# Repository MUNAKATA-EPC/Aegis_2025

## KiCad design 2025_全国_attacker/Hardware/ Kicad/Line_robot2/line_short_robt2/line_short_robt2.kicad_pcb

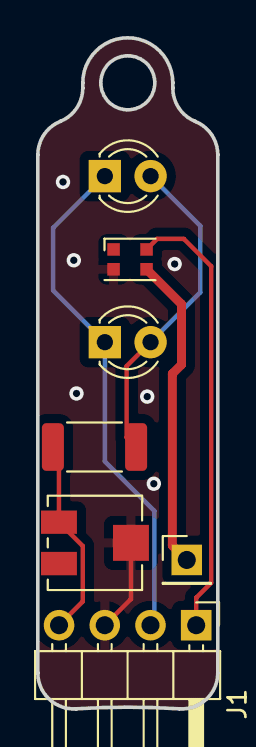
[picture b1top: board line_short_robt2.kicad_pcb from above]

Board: 2 copper layers, 10.0 x 37.3 mm, 7 parts (0 on the bottom side), 6 nets.

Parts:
D1: NeoPixel_THT; LED_WS2812B-2020_PLCC4_2.0x2.0mm
J1: Conn_01x04_Pin; PinHeader_1x04_P2.54mm_Horizontal
J2: Conn_01x01_Pin; PinHeader_1x01_P2.54mm_Vertical
Q1, Q2: Q_Photo_NPN; LED_D3.0mm_Clear
R1: 1K; R_2010_5025Metric
RV1: R_Potentiometer_Trim_US; Potentiometer_Vishay_TS53YJ_Vertical

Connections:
+3.3V: J1.2, Q1.1 (C), Q2.1 (C)
+5V: D1.3 (VDD), J2.1
/PWM: D1.4 (DIN), J1.1
/S: J1.4, R1.1, RV1.3
GND: D1.2 (GND), J1.3, RV1.2
unnamed: Q1.2 (E), Q2.2 (E), R1.2

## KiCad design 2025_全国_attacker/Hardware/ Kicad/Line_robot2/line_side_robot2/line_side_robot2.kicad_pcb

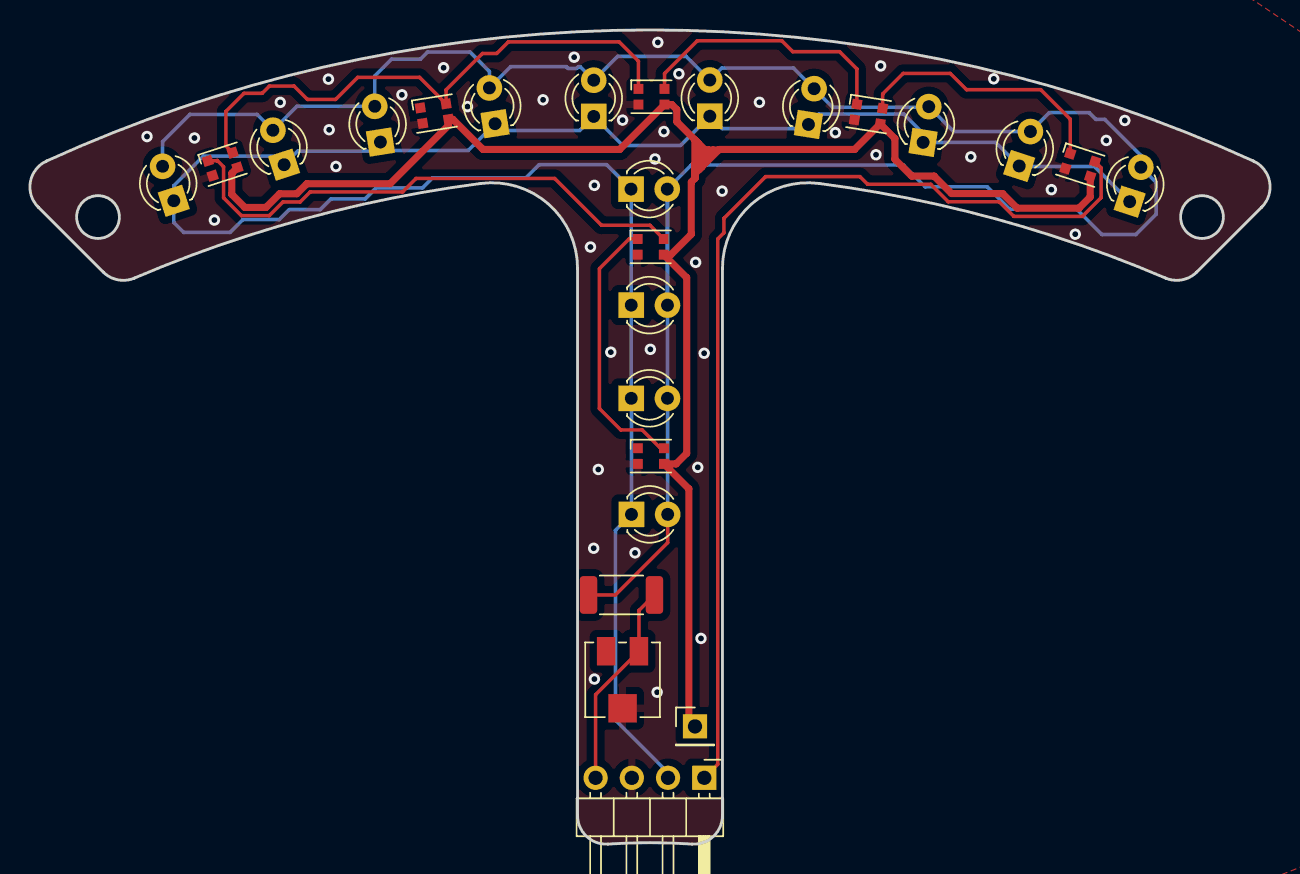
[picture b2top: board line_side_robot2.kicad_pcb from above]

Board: 2 copper layers, 87.0 x 57.1 mm, 25 parts (0 on the bottom side), 11 nets.

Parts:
D1, D2, D3, D4, D4#2, D5, D6: NeoPixel_THT; LED_WS2812B-2020_PLCC4_2.0x2.0mm
J1: Conn_01x04_Pin; PinHeader_1x04_P2.54mm_Horizontal
J2: Conn_01x01_Pin; PinHeader_1x01_P2.54mm_Vertical
Q1, Q2, Q3, Q4, Q5, Q6, Q7, Q8, Q9, Q10, Q11, Q12, Q13, Q14: Q_Photo_NPN; LED_D3.0mm_Clear
R1: 1K; R_2010_5025Metric
RV1: R_Potentiometer_Trim_US; Potentiometer_Vishay_TS53YJ_Vertical

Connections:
+3.3V: J1.2, Q1.1 (C), Q2.1 (C), Q3.1 (C), Q4.1 (C), Q5.1 (C), Q6.1 (C), Q7.1 (C), Q8.1 (C), Q9.1 (C), Q10.1 (C), Q11.1 (C), Q12.1 (C), Q13.1 (C), Q14.1 (C)
+5V: D1.3 (VDD), D2.3 (VDD), D3.3 (VDD), D4.3 (VDD), D4#2.3 (VDD), D5.3 (VDD), D6.3 (VDD), J2.1
/PWM: D1.4 (DIN), J1.1
/S: J1.4, R1.1, RV1.3
GND: D1.2 (GND), D2.2 (GND), D3.2 (GND), D4.2 (GND), D4#2.2 (GND), D5.2 (GND), D6.2 (GND), J1.3, RV1.2
unnamed: D1.1 (DOUT), D2.4 (DIN)
unnamed: D2.1 (DOUT), D3.4 (DIN)
unnamed: D3.1 (DOUT), D4.4 (DIN), D6.4 (DIN)
unnamed: D4#2.4 (DIN), D6.1 (DOUT)
unnamed: D4#2.1 (DOUT), D5.4 (DIN)
unnamed: Q1.2 (E), Q2.2 (E), Q3.2 (E), Q4.2 (E), Q5.2 (E), Q6.2 (E), Q7.2 (E), Q8.2 (E), Q9.2 (E), Q10.2 (E), Q11.2 (E), Q12.2 (E), Q13.2 (E), Q14.2 (E), R1.2

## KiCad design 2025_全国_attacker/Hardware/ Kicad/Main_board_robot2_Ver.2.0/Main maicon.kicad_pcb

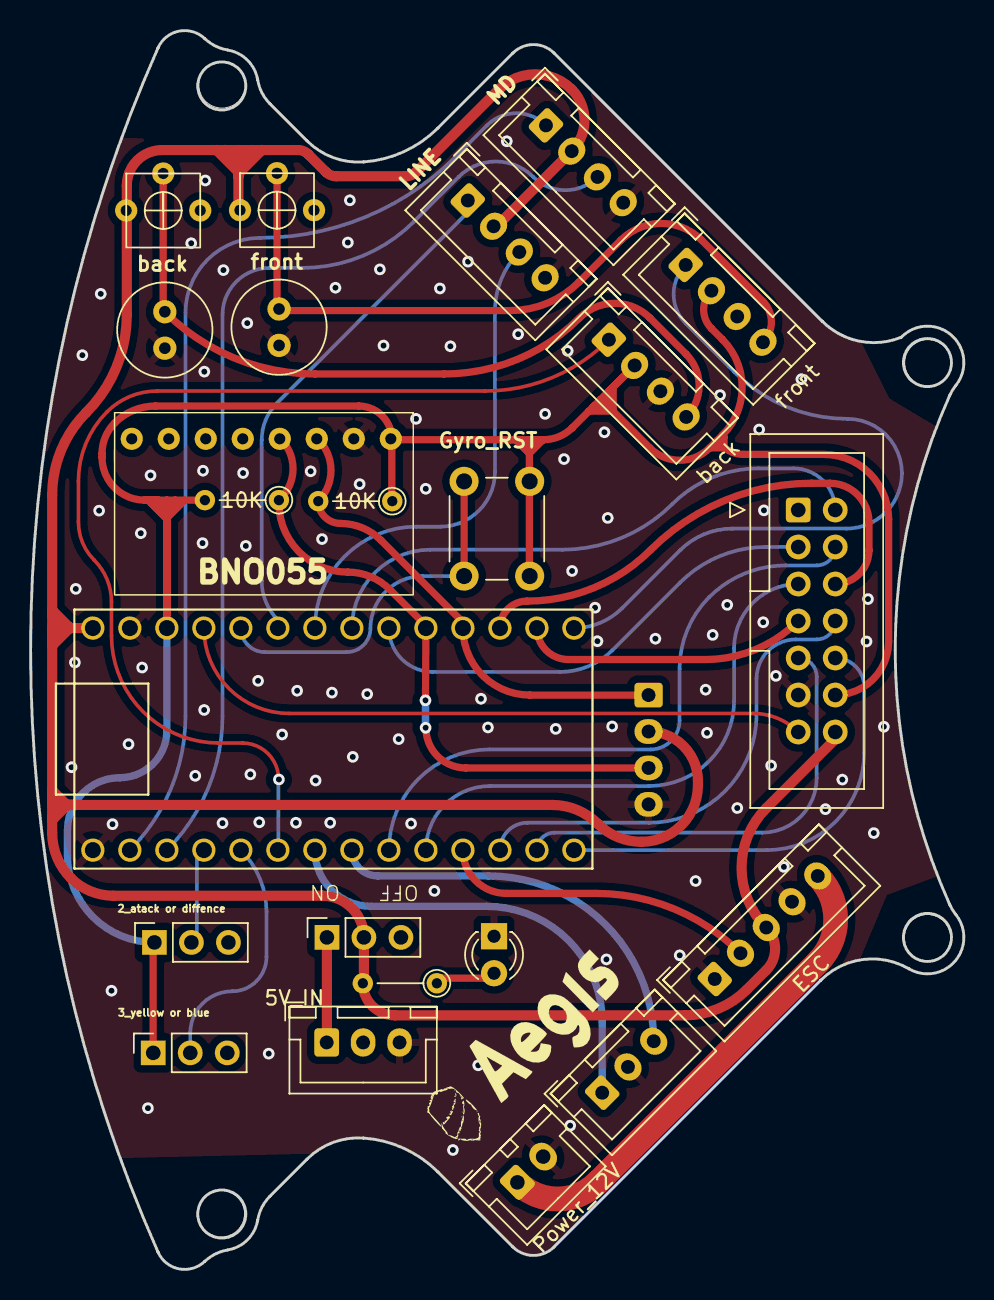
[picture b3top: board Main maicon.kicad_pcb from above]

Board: 2 copper layers, 64.1 x 85.0 mm, 24 parts (1 on the bottom side), 32 nets.

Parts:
BNO1: BNO00
C1, C2: C; C_Radial_D6.3mm_H5.0mm_P2.50mm
D1: LED; LED_D3.0mm_Clear
Gyro_RST: SW_Push; SW_PUSH_6mm_H5mm
J1: Power_12V; JST_XH_B2B-XH-A_1x02_P2.50mm_Vertical
J2: MD; JST_XH_B4B-XH-A_1x04_P2.50mm_Vertical
J3: Line; JST_XH_B4B-XH-A_1x04_P2.50mm_Vertical
J4: touch_sensor_1; JST_XH_B4B-XH-A_1x04_P2.50mm_Vertical
J5: Power_5V; JST_XH_B3B-XH-A_1x03_P2.50mm_Vertical
J6: ESC; JST_XH_B5B-XH-A_1x05_P2.50mm_Vertical
J7: Kicker; JST_XH_B3B-XH-A_1x03_P2.50mm_Vertical
J8: ESP32; IDC-Header_2x07_P2.54mm_Vertical
J9: touch_sensor_2; JST_XH_B4B-XH-A_1x04_P2.50mm_Vertical
J10: Gyro; JST_XH_B4B-XH-A_1x04_P2.50mm_Vertical
R1: R; R_Axial_DIN0204_L3.6mm_D1.6mm_P5.08mm_Vertical
R2, R3: 10K; R_Axial_DIN0204_L3.6mm_D1.6mm_P5.08mm_Vertical
RV1, RV3: R_Potentiometer_Trim_US; Variable_Register
SW1, SW2, SW3: SW_DPST_x2; PinSocket_1x03_P2.54mm_Vertical
U1: Teensy4.0; Teensy40

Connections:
5V_IN: J5.1, SW1.1 (A)
+3.3V: BNO1.1 (VIN), Gyro_RST.1, J4.2, J8.12, J9.2, R2.1, R3.2, SW2.1 (A), SW3.1 (A), U1.31 (3V3)
+5V: J2.2, J3.2, J6.3, J8.14, J10.2, R1.2, RV1.1, RV3.1, SW1.2 (B), U1.33 (VIN)
+12V: J1.1, J6.5
CN1_Touch_sensor: J4.1, U1.20 (13_SCK_CRX1_LED)
CN2_Touch_sensor: J9.1, U1.6 (4_BCLK2)
ESC: J6.2, U1.11 (9_OUT1C)
FET1: J7.1, U1.7 (5_IN2)
FET2: J7.3, U1.8 (6_OUT1D)
GND: BNO1.2 (GND), C1.1, C2.1, D1.1 (K), J1.2, J2.4, J3.4, J4.3, J5.3, J6.1, J6.4, J7.2, J8.11, J9.3, J10.4, U1.1 (GND), U1.32 (GND)
Gyro_reset: Gyro_RST.2, U1.29 (22_A8_CTX1)
LCD-TeensyD10: J8.8, U1.12 (10_CS_MQSR)
LCD-TeensyD11: J8.9, U1.13 (11_MOSI_CTX1)
LCD-TeensyD12: J8.10, U1.14 (12_MISO_MQSL)
LED1: C1.2, J4.4, RV1.2
LED2: C2.2, J9.4, RV3.2
unnamed: D1.2 (A), R1.1
RX_Ball: J8.5, U1.10 (8_TX2_IN1)
RX_Gyro_SDA: BNO1.4 (SDA), J10.3, R3.1, U1.24 (17_A3_TX4_SDA1)
RX_Line: J3.3, U1.27 (20_A6_TX5_LRCLK1)
RX_MD: J2.3, U1.3 (1_TX1_CTX2_MISO1)
RX_camera: J8.7, U1.21 (14_A0_TX3_SPDIF_OUT)
SCL_LCD: J8.2, U1.26 (19_A5_SCL0)
SDA_LCD: J8.3, U1.25 (18_A4_SDA0)
TX_Ball: J8.4, U1.9 (7_RX2_OUT1A)
TX_Gyro_SCL: BNO1.3 (SCL), J10.1, R2.2, U1.23 (16_A2_RX4_SCL1)
TX_Line: J3.1, U1.28 (21_A7_RX5_BCLK1)
TX_MD: J2.1, U1.2 (0_RX1_CRX2_CS1)
TX_camera: J8.6, U1.22 (15_A1_RX3_SPDIF_IN)
Tougle_Switch_atack or diffence: SW2.2 (B), U1.4 (2_OUT2)
Tougle_switch_ yellow or blue: SW3.2 (B), U1.5 (3_LRCLK2)
switch: J8.13, U1.30 (23_A9_CRX1_MCLK1)

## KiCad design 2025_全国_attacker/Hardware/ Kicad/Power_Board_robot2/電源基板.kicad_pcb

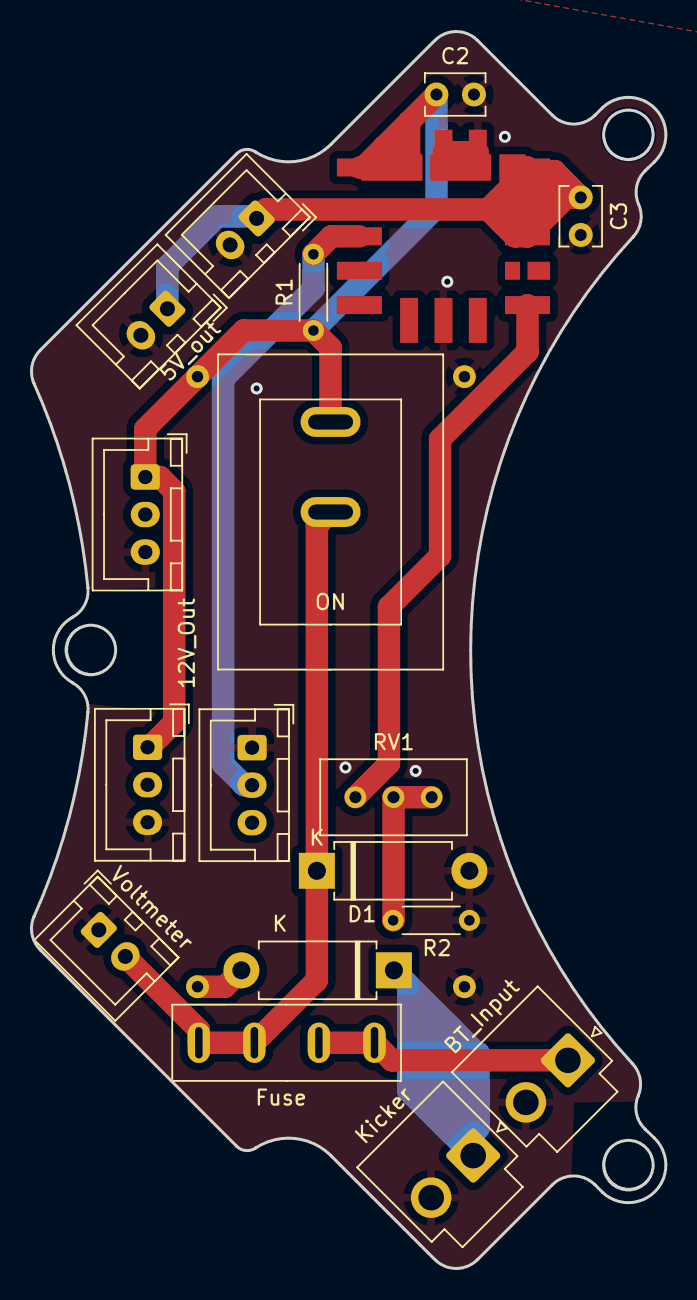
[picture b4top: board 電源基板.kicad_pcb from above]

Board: 2 copper layers, 42.3 x 82.4 mm, 19 parts (1 on the bottom side), 10 nets.

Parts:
5V_out: Conn_01x02_Socket; JST_XH_B2B-XH-A_1x02_P2.50mm_Vertical
12V_Out: Conn_01x03_Socket; JST_XH_B3B-XH-A_1x03_P2.50mm_Vertical
BT_Input: Battery; JST_VH_B2P-VH_1x02_P3.96mm_Vertical
C2, C3: C; C_Disc_D3.8mm_W2.6mm_P2.50mm
D1, D2: D; D_DO-15_P10.16mm_Horizontal
Fuse: Fuse; fuse_socket
J2: Conn_01x03_Socket; JST_XH_B3B-XH-A_1x03_P2.50mm_Vertical
J3: Conn_01x02_Socket; JST_VH_B2P-VH_1x02_P3.96mm_Vertical
J4: Conn_01x02_Socket; JST_XH_B2B-XH-A_1x02_P2.50mm_Vertical
R1, R2: R; R_Axial_DIN0204_L3.6mm_D1.6mm_P5.08mm_Horizontal
RV1: R_Potentiometer_Trim_US; Potentiometer_Bourns_3296W_Vertical
SW1: SW_DIP_x01; DS-850k
SW2: SW_DIP_x01; JST_XH_B3B-XH-A_1x03_P2.50mm_Vertical
U1: OKL-T_6-W12N-C; DCDC-murata-6A
U2: XL6009
Voltmeter: Conn_01x02_Socket; JST_XH_B2B-XH-A_1x02_P2.50mm_Vertical

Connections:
+5V: 5V_out.1, C3.1, J4.1, U1.4 (VOUT), U1.5 (SENSE)
+12V: 12V_Out.1, C2.1, J2.1, R1.1, SW1.2, U1.2 (VIN), U2.1 (IN＋)
+48V: D2.1 (K), J3.1
GND: 5V_out.2, 12V_Out.3, BT_Input.2 (-), C2.2, C3.2, D1.2 (A), J2.3, J3.2, J4.2, R2.2, SW2.1, U1.3 (GND), U1.7 (GND), U2.2 (IN－), U2.4 (OUT－), Voltmeter.1
unnamed: BT_Input.1 (+), Fuse.1
unnamed: D2.2 (A), U2.3 (OUT＋)
unnamed: R2.1, RV1.1, RV1.2
unnamed: R1.2, SW2.2, U1.1 (ON/OFF_CTRL)
unnamed: RV1.3, U1.6 (TRIM)
電圧計: D1.1 (K), Fuse.2, SW1.1, Voltmeter.2

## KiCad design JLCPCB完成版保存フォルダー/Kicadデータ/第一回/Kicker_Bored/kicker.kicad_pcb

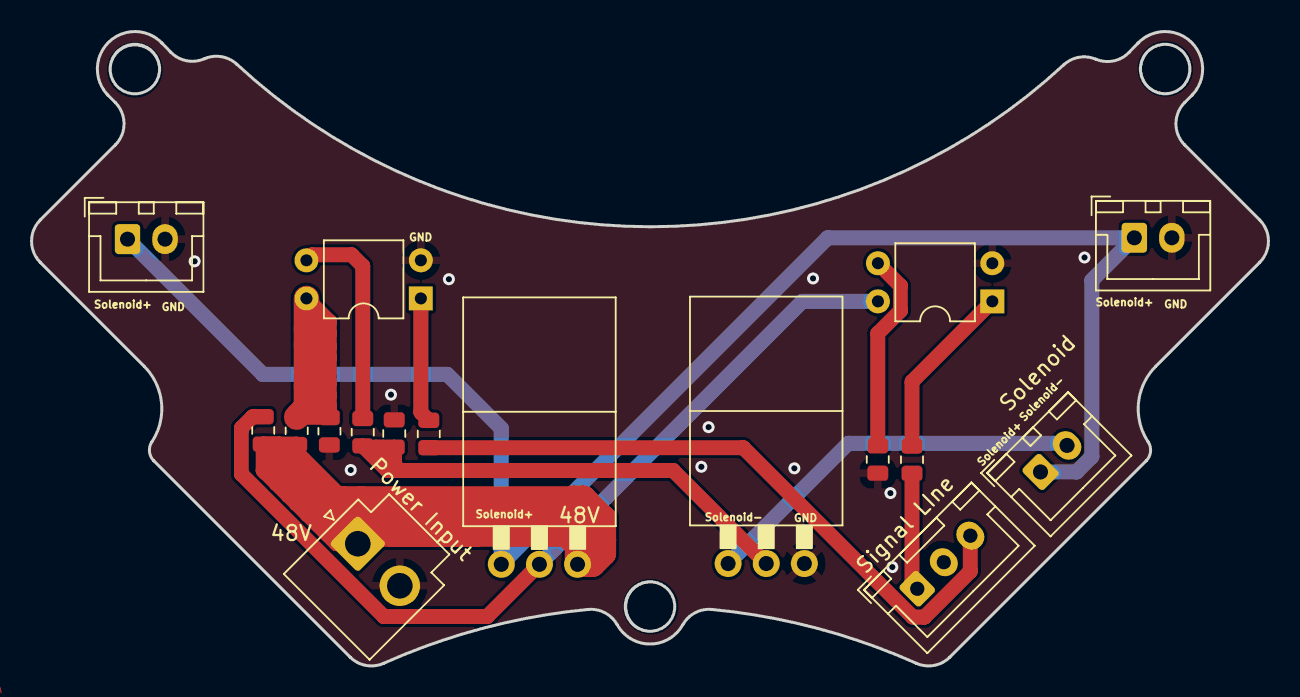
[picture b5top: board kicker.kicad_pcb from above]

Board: 2 copper layers, 82.4 x 42.3 mm, 17 parts (0 on the bottom side), 13 nets.

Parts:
C1, C2: C; JST_XH_B2B-XH-A_1x02_P2.50mm_Vertical
J1: Conn_01x02_Socket; JST_VH_B2P-VH_1x02_P3.96mm_Vertical
J3: Conn_01x03_Socket; JST_XH_B3B-XH-A_1x03_P2.50mm_Vertical
J4: Conn_01x02_Socket; JST_XH_B2B-XH-A_1x02_P2.50mm_Vertical
Q1: PMOS; K15A20D
Q3: NMOS; K15A20D
R1, R3, R8: 330K; R_0805_2012Metric
R2, R9: 1K; R_0805_2012Metric
R4: 10K; R_0805_2012Metric
R6, R7: 2K; R_0805_2012Metric
U1, U2: EL817; DIP-4_W7.62mm

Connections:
+15V: R7.2, R9.1, U2.4
+48V: J1.1, Q1.3 (S), R2.1, R7.1
FET1: J3.1, R1.1
FET２: J3.3, R8.1
GND: C1.2, C2.2, J1.2, J3.2, Q3.3 (S), R4.2, R6.2, R9.2, U1.2, U2.2
unnamed: Q1.2 (G), R2.2, U1.4
unnamed: Q3.2 (G), R3.1, R4.1
unnamed: R1.2, U1.1
unnamed: R3.2, U2.3
unnamed: R6.1, U1.3
unnamed: R8.2, U2.1
Solenoid+: C1.1, C2.1, J4.1, Q1.1 (D)
Solenoid-: J4.2, Q3.1 (D)

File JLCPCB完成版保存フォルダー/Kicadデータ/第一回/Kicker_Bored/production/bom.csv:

Designator,Footprint,Quantity,Value,LCSC Part #
"C1, C2",JST_XH_B2B-XH-A_1x02_P2.50mm_Vertical,2,C,
J1,JST_VH_B2P-VH_1x02_P3.96mm_Vertical,1,Conn_01x02_Socket,
J3,JST_XH_B3B-XH-A_1x03_P2.50mm_Vertical,1,Conn_01x03_Socket,
J4,JST_XH_B2B-XH-A_1x02_P2.50mm_Vertical,1,Conn_01x02_Socket,
Q1,K15A20D,1,PMOS,
Q3,K15A20D,1,NMOS,
"R1, R3, R8",0805,3,330K,
"R2, R9",0805,2,1K,
R4,0805,1,10K,
"R6, R7",0805,2,2K,
"U1, U2",DIP-4_W7.62mm,2,EL817,

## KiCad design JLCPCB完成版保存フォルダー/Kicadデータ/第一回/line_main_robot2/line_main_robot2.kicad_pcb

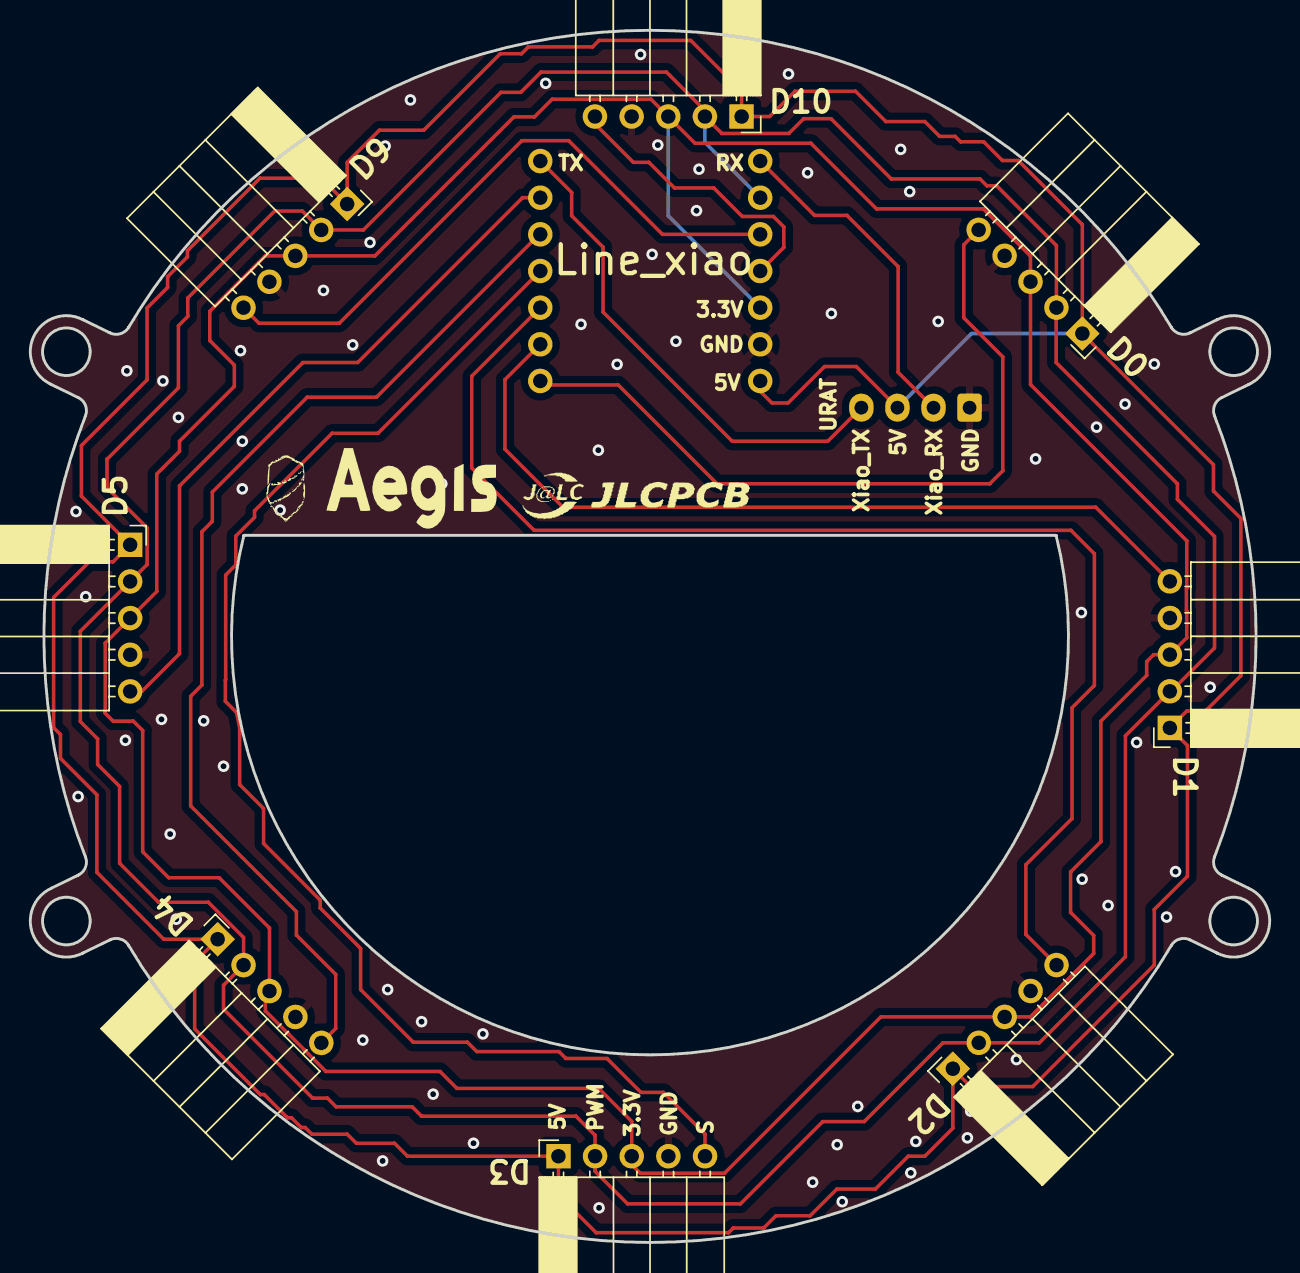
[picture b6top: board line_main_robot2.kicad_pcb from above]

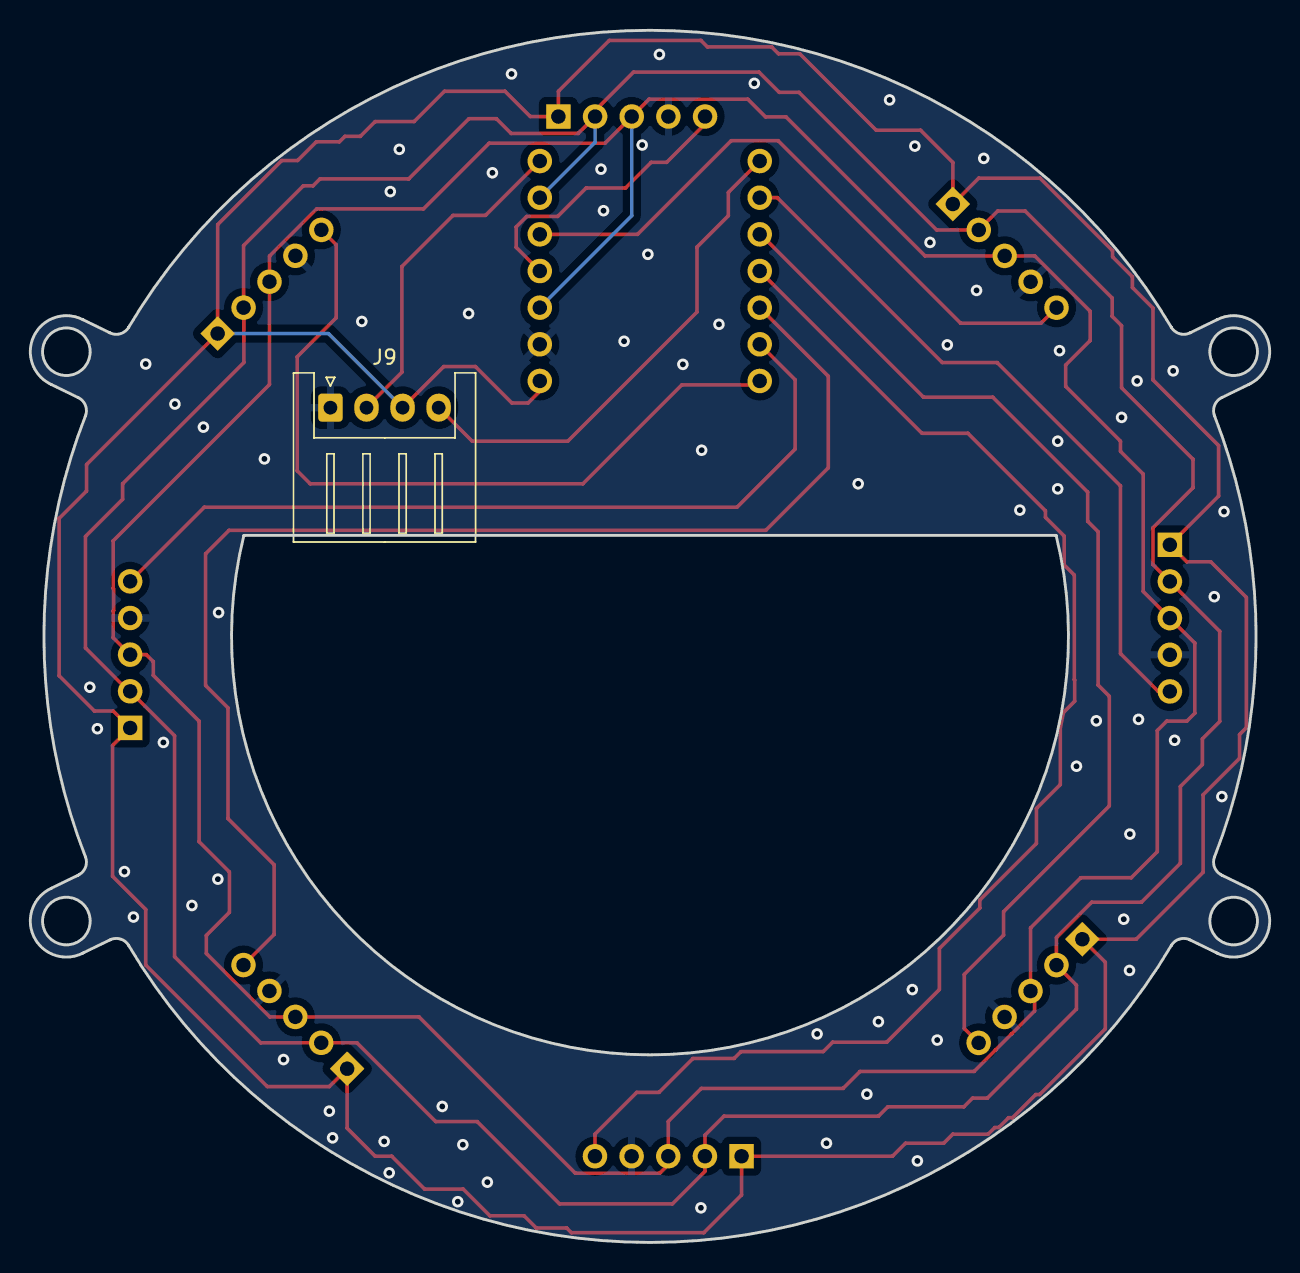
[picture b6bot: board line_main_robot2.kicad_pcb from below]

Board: 2 copper layers, 85.9 x 84.0 mm, 10 parts (2 on the bottom side), 14 nets.

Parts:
J1, J2, J3, J4, J5, J6, J7, J8: Conn_01x05_Pin; PinSocket_1x05_P2.54mm_Horizontal
J9: Serial; JST_XH_S4B-XH-A_1x04_P2.50mm_Horizontal
U1: Line_xiao; seeeduinoXIAO

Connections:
+3.3V: J1.3, J2.3, J3.3, J4.3, J5.3, J6.3, J7.3, J8.3, U1.12 (3V3)
+5V: J1.1, J2.1, J3.1, J4.1, J5.1, J6.1, J7.1, J8.1, J9.3, U1.14 (5V)
/1: J1.5, U1.1 (DAC)
/2: J2.5, U1.2
/3: J3.5, U1.3
/4: J4.5, U1.4
/5: J5.5, U1.5 (SDA)
/6: J6.5, U1.6 (SCL)
/7: J7.5, U1.10 (MISO)
/8: J8.5, U1.11 (MOSI)
/PWM: J1.2, J2.2, J3.2, J4.2, J5.2, J6.2, J7.2, J8.2, U1.9 (SCK)
/RX: J9.2, U1.8 (RX)
/TX: J9.4, U1.7 (TX)
GND: J1.4, J2.4, J3.4, J4.4, J5.4, J6.4, J7.4, J8.4, J9.1, U1.13 (GND)
